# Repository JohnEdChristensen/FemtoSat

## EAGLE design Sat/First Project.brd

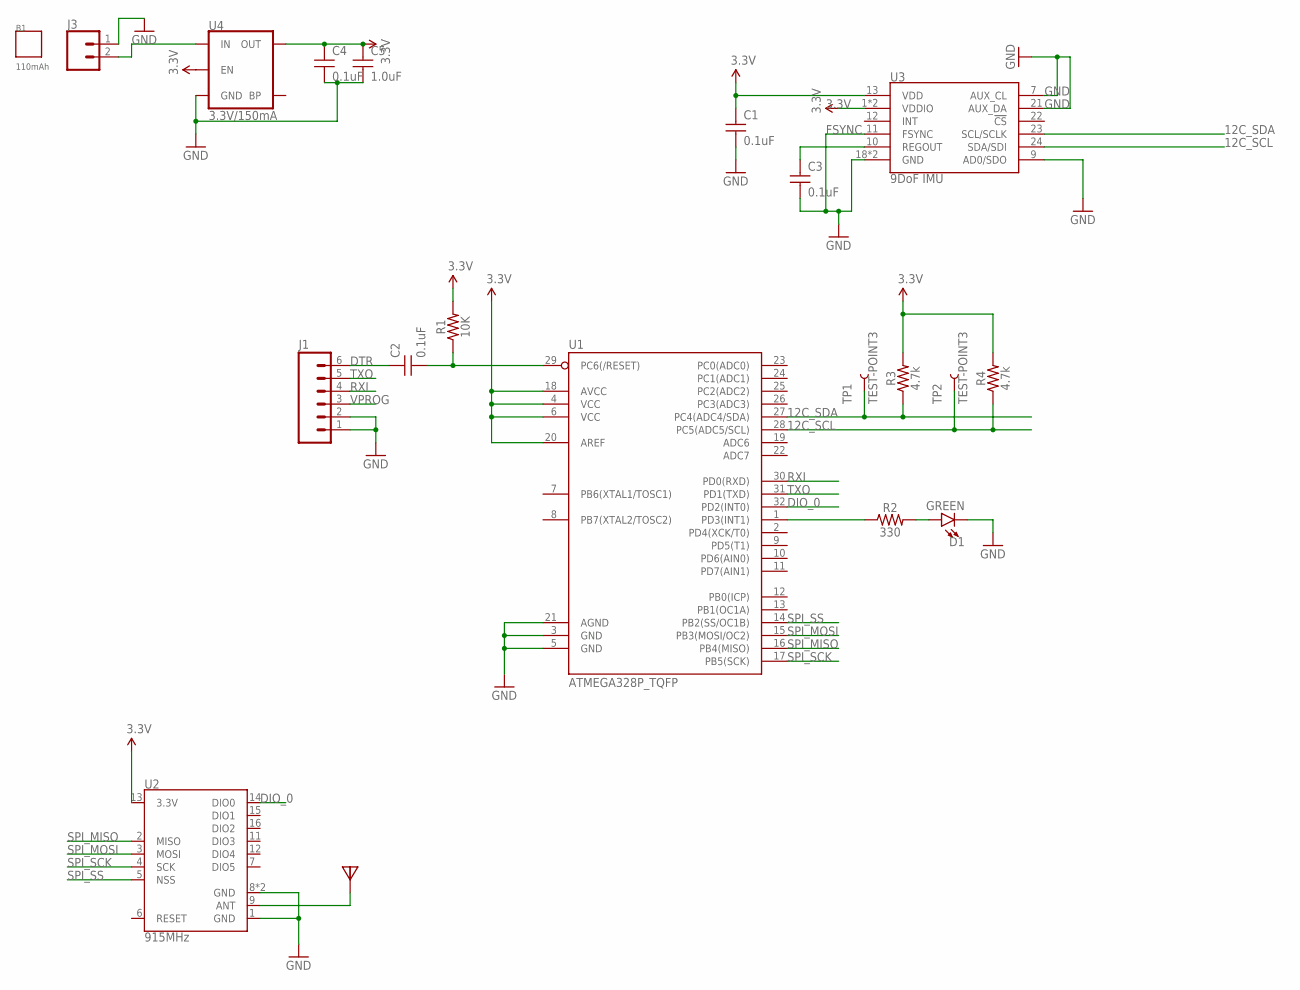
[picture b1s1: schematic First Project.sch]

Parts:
ANT1: ANTENNA_PAD; RFM12B-ANTENNA
B1: 110mAh; BATT_110MAH
C1, C2, C3, C4: 0.1uF; 0603-CAP
C5: 1.0uF; 0603
D1: GREEN; LED-0603
J1: CONNECTOR_6PINSILK_FEMALE_PTH; 1X06
J3: CONNECTOR_2PIN-JST-2MM-SMT; JST-2-SMD
R1: 10K; 0603-RES
R2: 330; 0603
R3, R4: 4.7k; 0603
TP1, TP2: TEST-POINT3; PAD.03X.03
U1: ATMEGA328P_TQFP; TQFP32-08
U2: 915MHz; RFM69HCW-XXXS2
U3: 9DoF IMU; QFN24-3X3
U4: 3.3V/150mA; SOT23-5

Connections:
3.3V: C1.1, C4.1, C5.1, R1.2, R3.2, R4.2, U1.4 (VCC), U1.6 (VCC), U1.18 (AVCC), U1.20 (AREF), U2.13 (3.3V), U3.1 (VDDIO), U3.8 (VDDIO), U3.13 (VDD), U4.3 (EN), U4.5 (OUT)
12C_SCL: R4.1, TP2.P$1, U1.28 (PC5(ADC5/SCL)), U3.24 (SDA/SDI)
12C_SDA: R3.1, TP1.P$1, U1.27 (PC4(ADC4/SDA)), U3.23 (SCL/SCLK)
DIO_0: U1.32 (PD2(INT0)), U2.14 (DIO0)
DTR: C2.1, J1.6
FSYNC: C3.1, U3.10 (REGOUT)
GND: C1.2, C3.2, C4.2, C5.2, D1.C, J1.1, J1.2, J3.1 (2), U1.3 (GND), U1.5 (GND), U1.21 (AGND), U2.1 (GND), U2.8 (GND), U2.10 (GND), U3.7 (AUX_CL), U3.9 (AD0/SDO), U3.11 (FSYNC), U3.18 (GND), U3.20 (GND), U3.21 (AUX_DA), U4.2 (GND)
unnamed: C2.2, R1.1, U1.29 (PC6(/RESET))
unnamed: J3.2 (1), U4.1 (IN)
unnamed: D1.A, R2.2
unnamed: ANT1.P$1, U2.9 (ANT)
unnamed: R2.1, U1.1 (PD3(INT1))
RXI: J1.4, U1.30 (PD0(RXD))
SPI_MISO: U1.16 (PB4(MISO)), U2.2 (MISO)
SPI_MOSI: U1.15 (PB3(MOSI/OC2)), U2.3 (MOSI)
SPI_SCK: U1.17 (PB5(SCK)), U2.4 (SCK)
SPI_SS: U1.14 (PB2(SS/OC1B)), U2.5 (NSS)
TXO: J1.5, U1.31 (PD1(TXD))
VPROG: J1.3

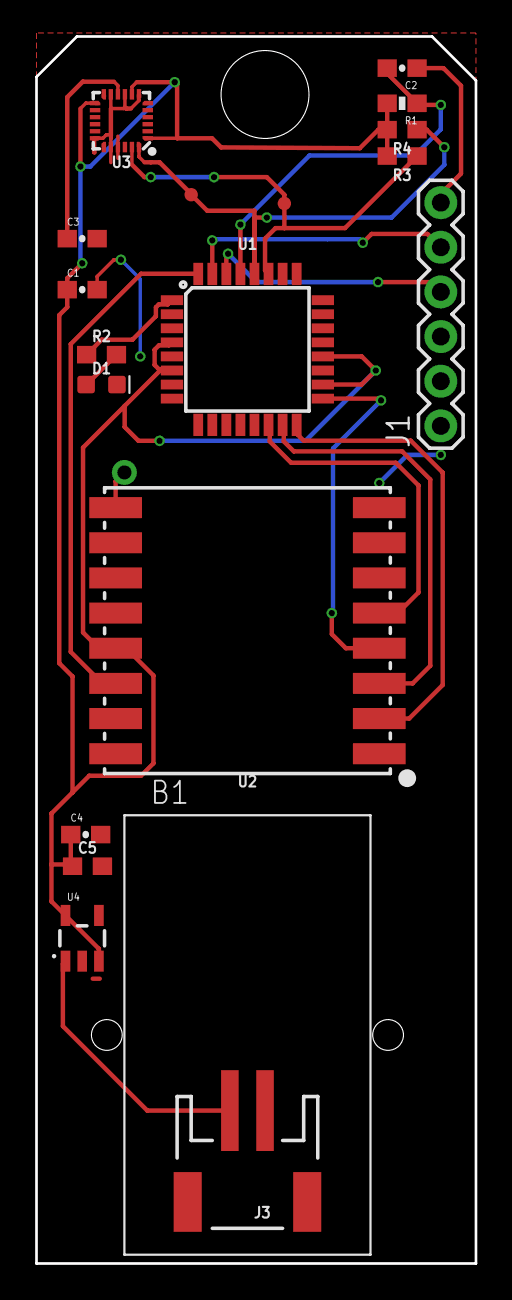
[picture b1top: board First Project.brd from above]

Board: 2 copper layers, 25.0 x 69.8 mm, 20 parts (0 on the bottom side), 18 nets.

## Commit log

2018-10-04 This is a commit message
2018-10-04 Test files for us
2018-10-04 hello friends
2018-10-11 Finished Schematic
2018-10-30 Routed Components and added a Ground Plane
2018-11-01 Cleaned up some routing
